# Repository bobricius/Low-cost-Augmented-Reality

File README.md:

# Low-cost-Augmented-Reality
Optimized for use microcontrollers and SPI displays popular ST7789 1.3" IPS 240x240 FEEL LIKE IRON MAN !!!!!

Something like Iron man helmet but can drive with simple arduino
Raspberry pi zero, PICO and more

- Driven with simple SPI interface
- Helmet cost about 30$ displays 10$
- 2x SPI IPS display 240x240 ST7789
- Easy drive with #samd21 #rp2040 #raspberrypi #ESP32
- no complicated HDMI
- beautiful and clear image in all you view
- LOW power about 60mA including SAMD21 MCU
- parallel or separated (for 3D) display driving
- USB OTG

YOU CAN TYPE ON KEYBOARD AND DIRECT READ MESSAGES :D

-module also have prepared LoRa radio for sending/receiving messages and GPS

TODO:
- Adjustable distance between displays (flex cable or solder bridge)
- Test on Raspbery pi zero
- select nice 8pin cable/connector etc. USB-C with custom pinout

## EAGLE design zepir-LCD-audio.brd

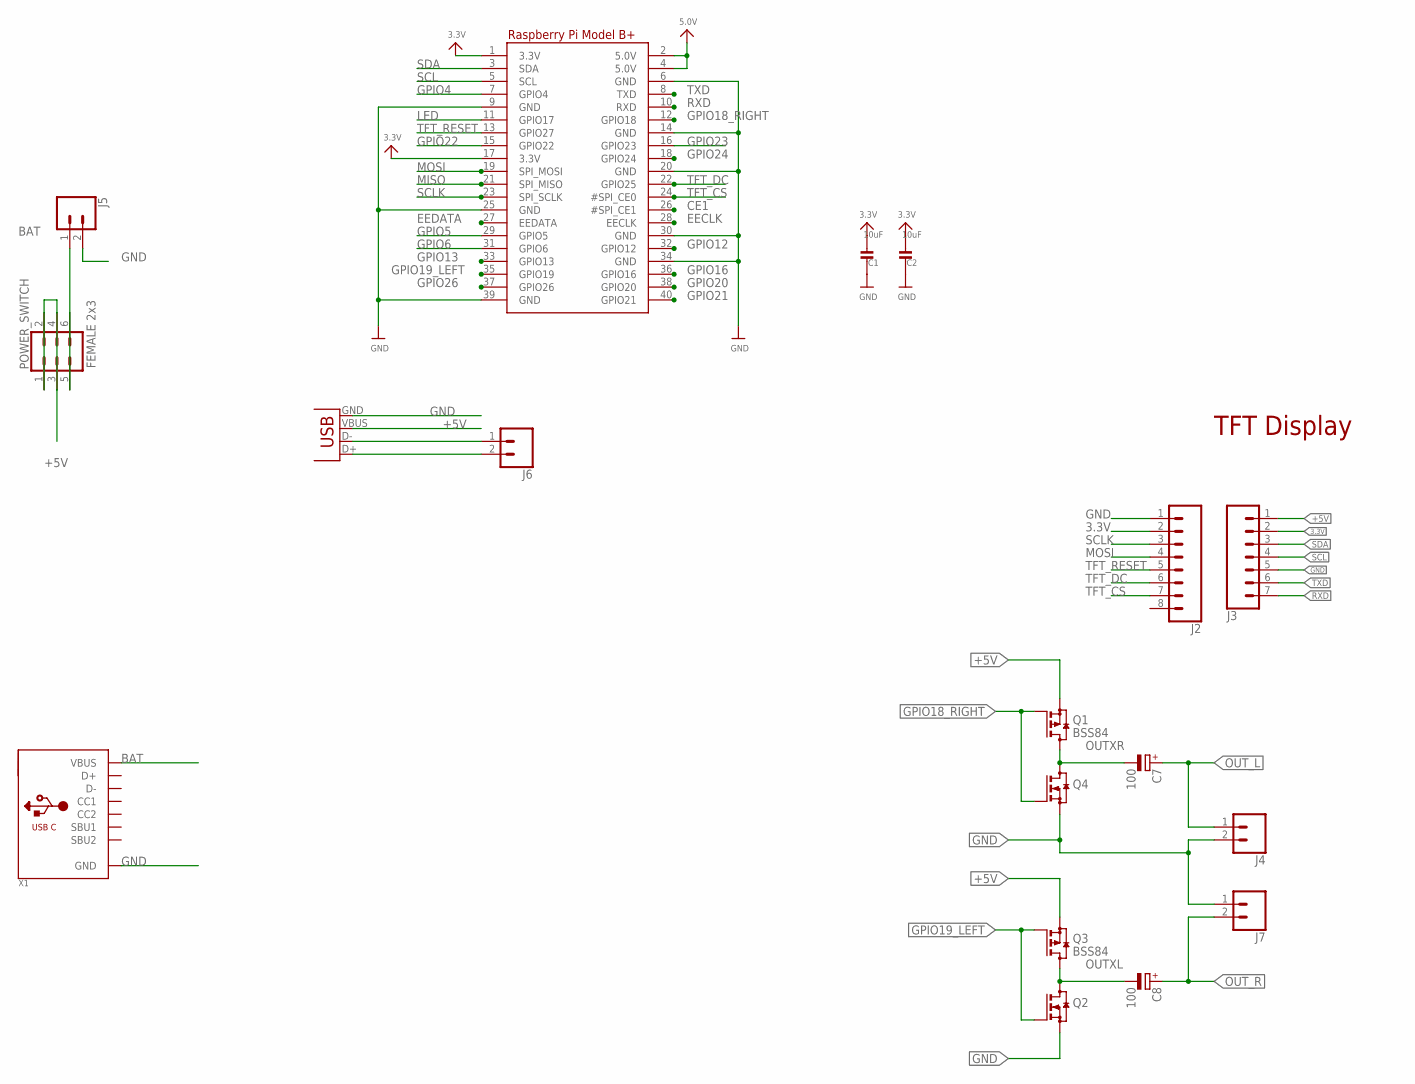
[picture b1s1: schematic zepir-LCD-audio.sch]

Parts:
C1, C2: 10uF; _1206
C7, C8: 100; B/3528-21R
J2: CONN_08LONGPADS; 1X08_LONGPADS
J3: CONN_07LONGPADS; 1X07_LONGPADS
J4, J5, J7: CONN_02PTH3; 1X02_LONGPADS
J6: CONN_02; 1X02
POWER_SWITCH: FEMALE 2x3; 2X3
Q1, Q3: BSS84; SOT23
Q2, Q4: BSS123; SOT23
RPI1: RASPBERRYPI_BPLUS_BONNETNODIM; PI_BONNET_NODIM
USBIN1: USB-A-SMD; USB-A-S-NOSILK-FEMALE
X1: USB_C; USB_C_CUSB31-CFM2AX-01-X

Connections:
3.3V: C1.2, C2.2, J2.2, J3.2, RPI1.1 (3.3V), RPI1.17 (3.3V)
+5V: J3.1, POWER_SWITCH.1, POWER_SWITCH.2, POWER_SWITCH.3, POWER_SWITCH.4, Q1.2 (S), Q3.2 (S), RPI1.2 (5.0V), RPI1.4 (5.0V), USBIN1.VBUS
BAT: J5.1, POWER_SWITCH.5, POWER_SWITCH.6, X1.A4B9 (VBUS), X1.B4A9 (VBUS)
CE1: RPI1.26 (#SPI_CE1)
DM: J6.1, USBIN1.D-
DP: J6.2, USBIN1.D+
EECLK: RPI1.28 (EECLK)
EEDATA: RPI1.27 (EEDATA)
GND: C1.1, C2.1, J2.1, J3.5, J4.2, J5.2, J7.1, Q2.2 (S), Q4.2 (S), RPI1.6 (GND), RPI1.9 (GND), RPI1.14 (GND), RPI1.20 (GND), RPI1.25 (GND), RPI1.30 (GND), RPI1.34 (GND), RPI1.39 (GND), USBIN1.GND, X1.A1B12 (GND), X1.B1A12 (GND)
GPIO4: RPI1.7 (GPIO4)
GPIO5: RPI1.29 (GPIO5)
GPIO6: RPI1.31 (GPIO6)
GPIO12: RPI1.32 (GPIO12)
GPIO13: RPI1.33 (GPIO13)
GPIO16: RPI1.36 (GPIO16)
GPIO18_RIGHT: Q1.1 (G), Q4.1 (G), RPI1.12 (GPIO18)
GPIO19_LEFT: Q2.1 (G), Q3.1 (G), RPI1.35 (GPIO19)
GPIO20: RPI1.38 (GPIO20)
GPIO21: RPI1.40 (GPIO21)
GPIO22: RPI1.15 (GPIO22)
GPIO23: RPI1.16 (GPIO23)
GPIO24: RPI1.18 (GPIO24)
GPIO26: RPI1.37 (GPIO26)
LED: RPI1.11 (GPIO17)
MISO: RPI1.21 (SPI_MISO)
MOSI: J2.4, RPI1.19 (SPI_MOSI)
OUTXL: C8.-, Q2.3 (D), Q3.3 (D)
OUTXR: C7.-, Q1.3 (D), Q4.3 (D)
OUT_L: C7.+, J4.1
OUT_R: C8.+, J7.2
RXD: J3.7, RPI1.10 (RXD)
SCL: J3.4, RPI1.5 (SCL)
SCLK: J2.3, RPI1.23 (SPI_SCLK)
SDA: J3.3, RPI1.3 (SDA)
TFT_CS: J2.7, RPI1.24 (#SPI_CE0)
TFT_DC: J2.6, RPI1.22 (GPIO25)
TFT_RESET: J2.5, RPI1.13 (GPIO27)
TXD: J3.6, RPI1.8 (TXD)

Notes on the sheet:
TFT Display

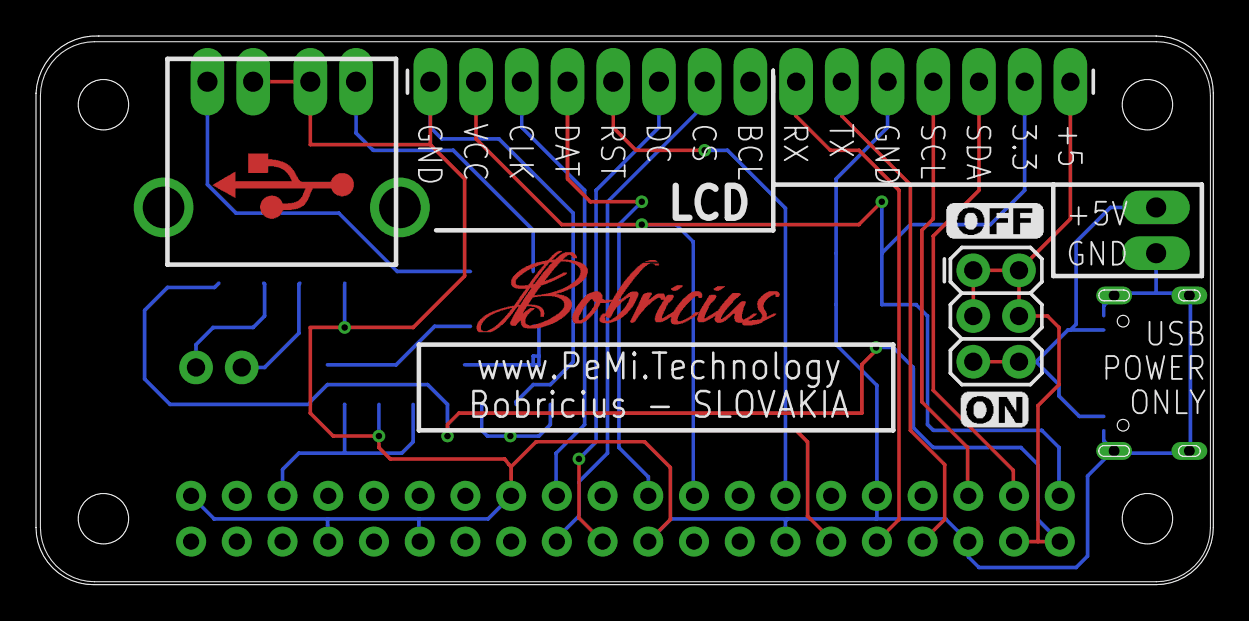
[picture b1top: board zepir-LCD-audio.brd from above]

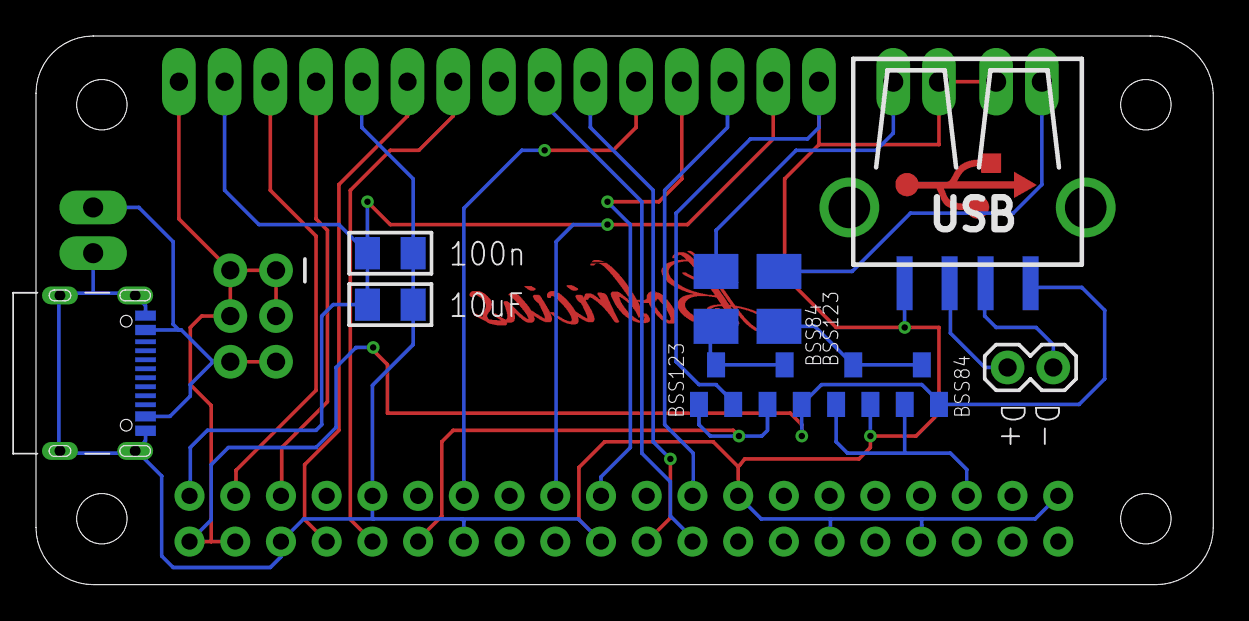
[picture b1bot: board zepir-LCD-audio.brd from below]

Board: 2 copper layers, 65.4 x 30.5 mm, 18 parts (11 on the bottom side), 21 nets.

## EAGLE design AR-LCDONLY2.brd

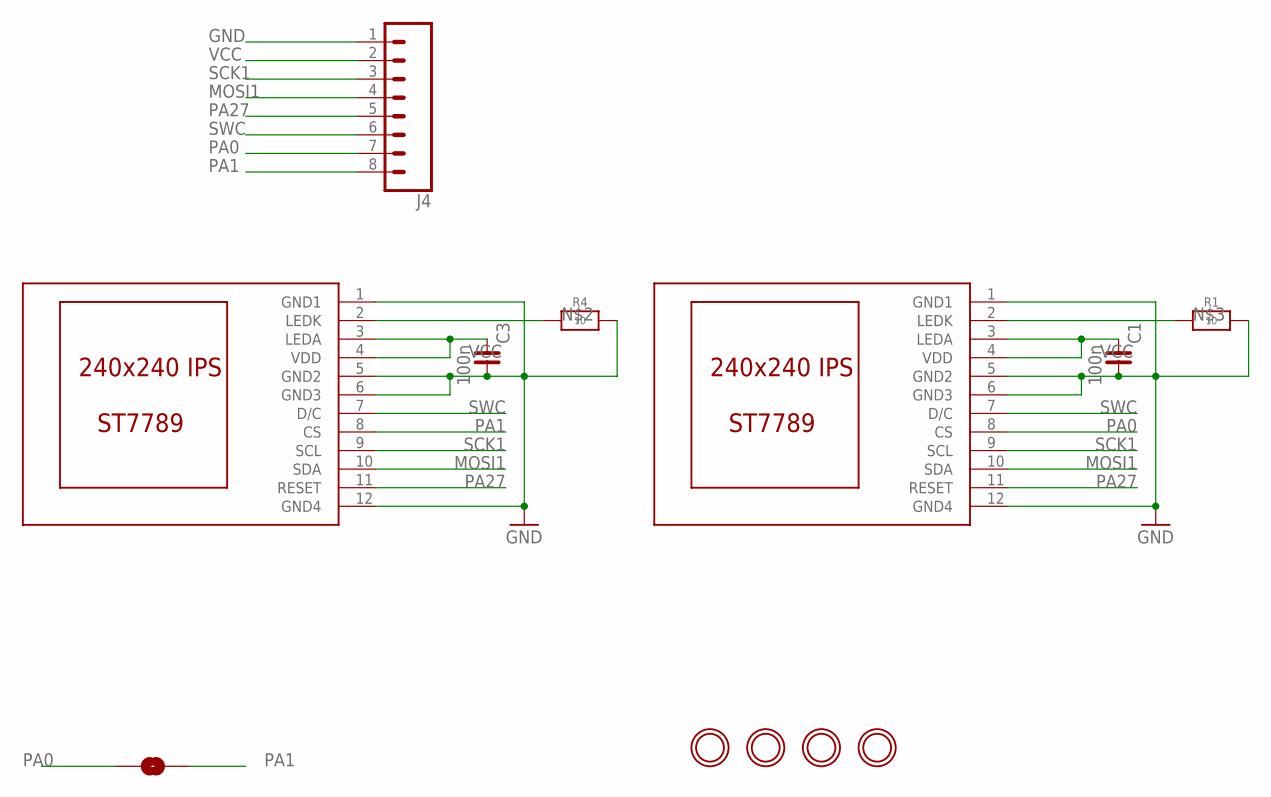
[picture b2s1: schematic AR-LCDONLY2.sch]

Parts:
C1, C3: 100n; C0805
J4: CONN_08LONGPADS; 1X08_LONGPADS
JUMPER1: SOLDERJUMPERNC2; SJ_2S-NOTRACE
R1, R4: 10; _0805MP
U$1, U$39: DISP_LCD_0.9IN_160X80; TFT_0.96IN_160X80
U$2, U$3, U$4, U$10: MOUNTINGHOLE2.0; MOUNTINGHOLE_2.0_PLATED

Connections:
GND: C1.1, C3.1, J4.1, R1.2, R4.2, U$1.1 (GND1), U$1.5 (GND2), U$1.6 (GND3), U$1.12 (GND4), U$39.1 (GND1), U$39.5 (GND2), U$39.6 (GND3), U$39.12 (GND4)
MOSI1: J4.4, U$1.10 (SDA), U$39.10 (SDA)
unnamed: R4.1, U$39.2 (LEDK)
unnamed: R1.1, U$1.2 (LEDK)
PA0: J4.7, JUMPER1.2, U$1.8 (CS)
PA1: J4.8, JUMPER1.1, U$39.8 (CS)
PA27: J4.5, U$1.11 (RESET), U$39.11 (RESET)
SCK1: J4.3, U$1.9 (SCL), U$39.9 (SCL)
SWC: J4.6, U$1.7 (D/C), U$39.7 (D/C)
VCC: C1.2, C3.2, J4.2, U$1.3 (LEDA), U$1.4 (VDD), U$39.3 (LEDA), U$39.4 (VDD)

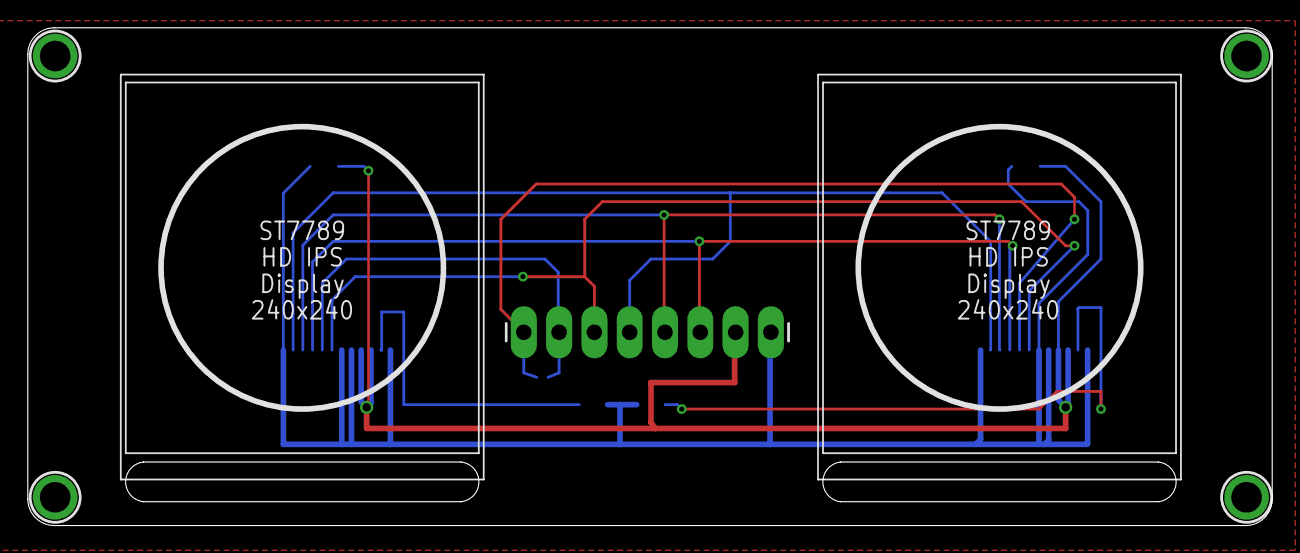
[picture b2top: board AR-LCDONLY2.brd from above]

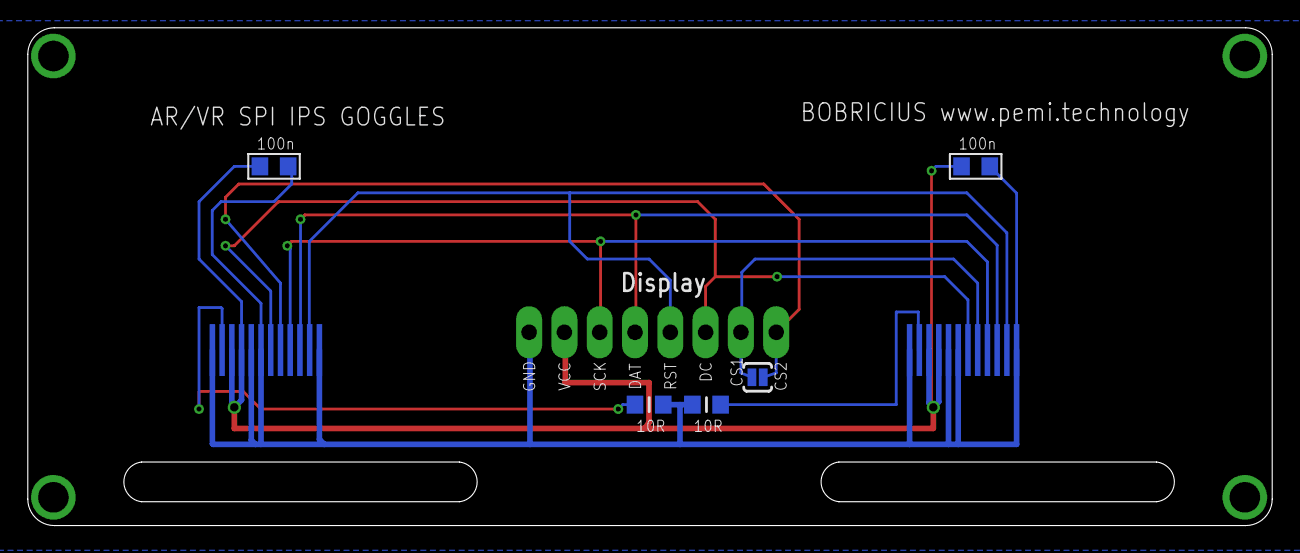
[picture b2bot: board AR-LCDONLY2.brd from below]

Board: 2 copper layers, 89.5 x 35.8 mm, 12 parts (5 on the bottom side), 10 nets.

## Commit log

2022-04-19 Universal SPI hat for Raspberry pi ZERO

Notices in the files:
parts and their libraries:
SparkFun-Connectors: Licensing: Creative Commons ShareAlike 4.0 International - https://creativecommons.org/licenses/by-sa/4.0
SparkFun: Licensing: CC v3.0 Share-Alike You are welcome to use this library for commercial purposes.
